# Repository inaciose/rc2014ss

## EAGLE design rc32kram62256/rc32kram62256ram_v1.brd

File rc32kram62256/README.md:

# CNC 3018 - RC2014 - 32K RAM BOARD

This board is done following the schematics of the official RC2014-32K RAM (now retired)

ICs
- 62256 RAM
- 74LS32
- 74LS04

Sockets
- 1 x 28 pin wide DIL
- 1 x 14 pin narrow DIL

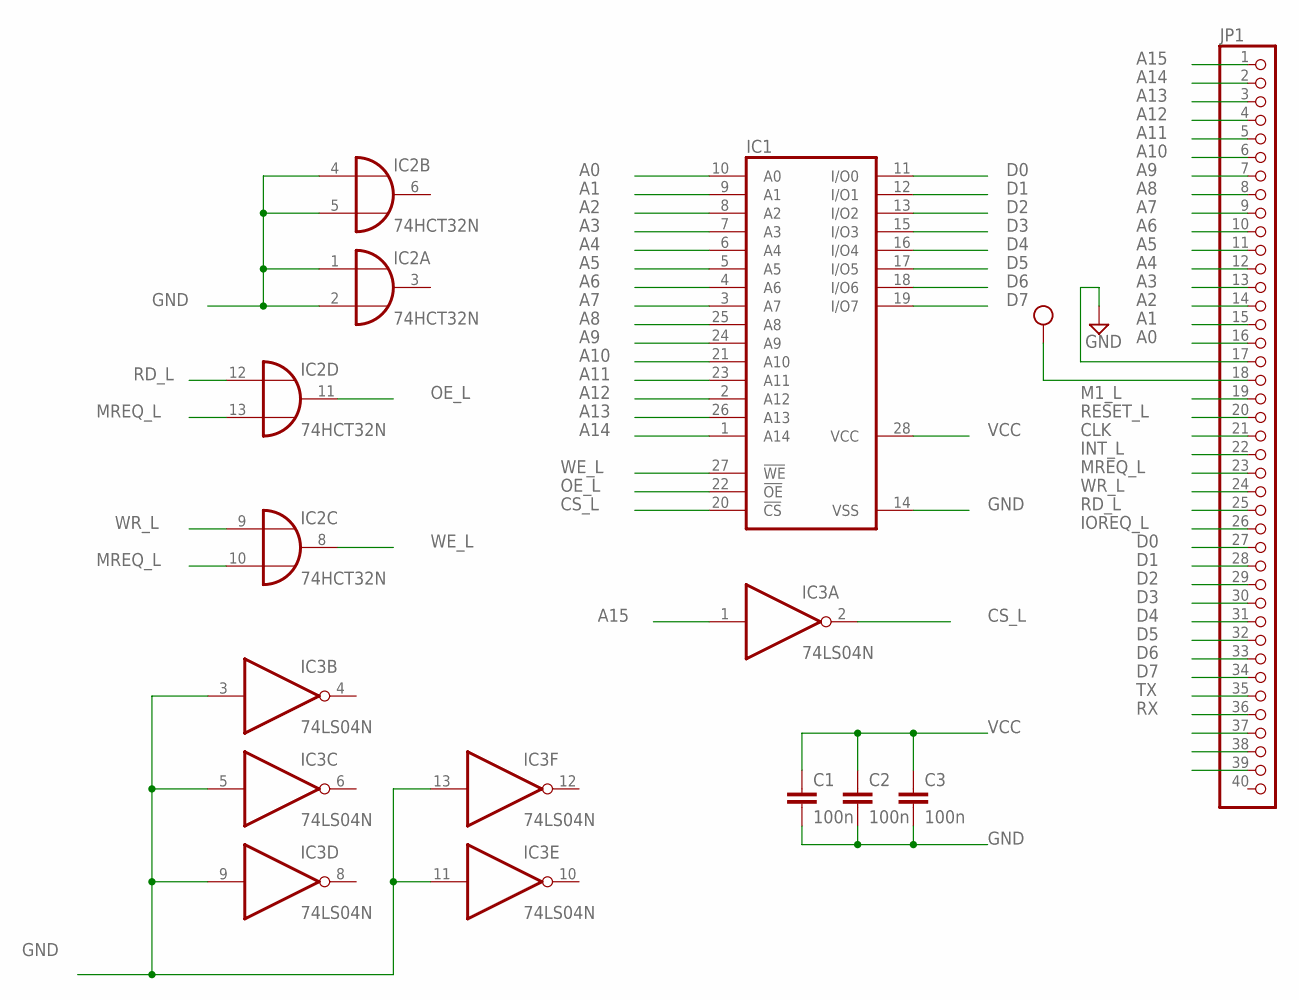
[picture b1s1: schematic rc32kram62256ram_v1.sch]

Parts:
C1, C2, C3: 100n; C050-025X075
IC1: 62256P; DIL28-6
IC2: 74HCT32N; DIL14
IC3: 74LS04N; DIL14
JP1: PINHD-1X40; 1X40

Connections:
A0: IC1.10 (A0), JP1.16
A1: IC1.9 (A1), JP1.15
A2: IC1.8 (A2), JP1.14
A3: IC1.7 (A3), JP1.13
A4: IC1.6 (A4), JP1.12
A5: IC1.5 (A5), JP1.11
A6: IC1.4 (A6), JP1.10
A7: IC1.3 (A7), JP1.9
A8: IC1.25 (A8), JP1.8
A9: IC1.24 (A9), JP1.7
A10: IC1.21 (A10), JP1.6
A11: IC1.23 (A11), JP1.5
A12: IC1.2 (A12), JP1.4
A13: IC1.26 (A13), JP1.3
A14: IC1.1 (A14), JP1.2
A15: IC3.1 (I), JP1.1
CLK: JP1.21
CS_L: IC1.20 (!CS), IC3.2 (O)
D0: IC1.11 (I/O0), JP1.27
D1: IC1.12 (I/O1), JP1.28
D2: IC1.13 (I/O2), JP1.29
D3: IC1.15 (I/O3), JP1.30
D4: IC1.16 (I/O4), JP1.31
D5: IC1.17 (I/O5), JP1.32
D6: IC1.18 (I/O6), JP1.33
D7: IC1.19 (I/O7), JP1.34
GND: C1.2, C2.2, C3.2, IC1.14 (VSS), IC2.1 (I0), IC2.2 (I1), IC2.4 (I0), IC2.5 (I1), IC2.7 (GND), IC3.3 (I), IC3.5 (I), IC3.7 (GND), IC3.9 (I), IC3.11 (I), IC3.13 (I), JP1.17
INT_L: JP1.22
IOREQ_L: JP1.26
M1_L: JP1.19
MREQ_L: IC2.10 (I1), IC2.13 (I1), JP1.23
OE_L: IC1.22 (!OE), IC2.11 (O)
RD_L: IC2.12 (I0), JP1.25
RESET_L: JP1.20
RX: JP1.36
TX: JP1.35
VCC: C1.1, C2.1, C3.1, IC1.28 (VCC), IC2.14 (VCC), IC3.14 (VCC), JP1.18
WE_L: IC1.27 (!WE), IC2.8 (O)
WR_L: IC2.9 (I0), JP1.24

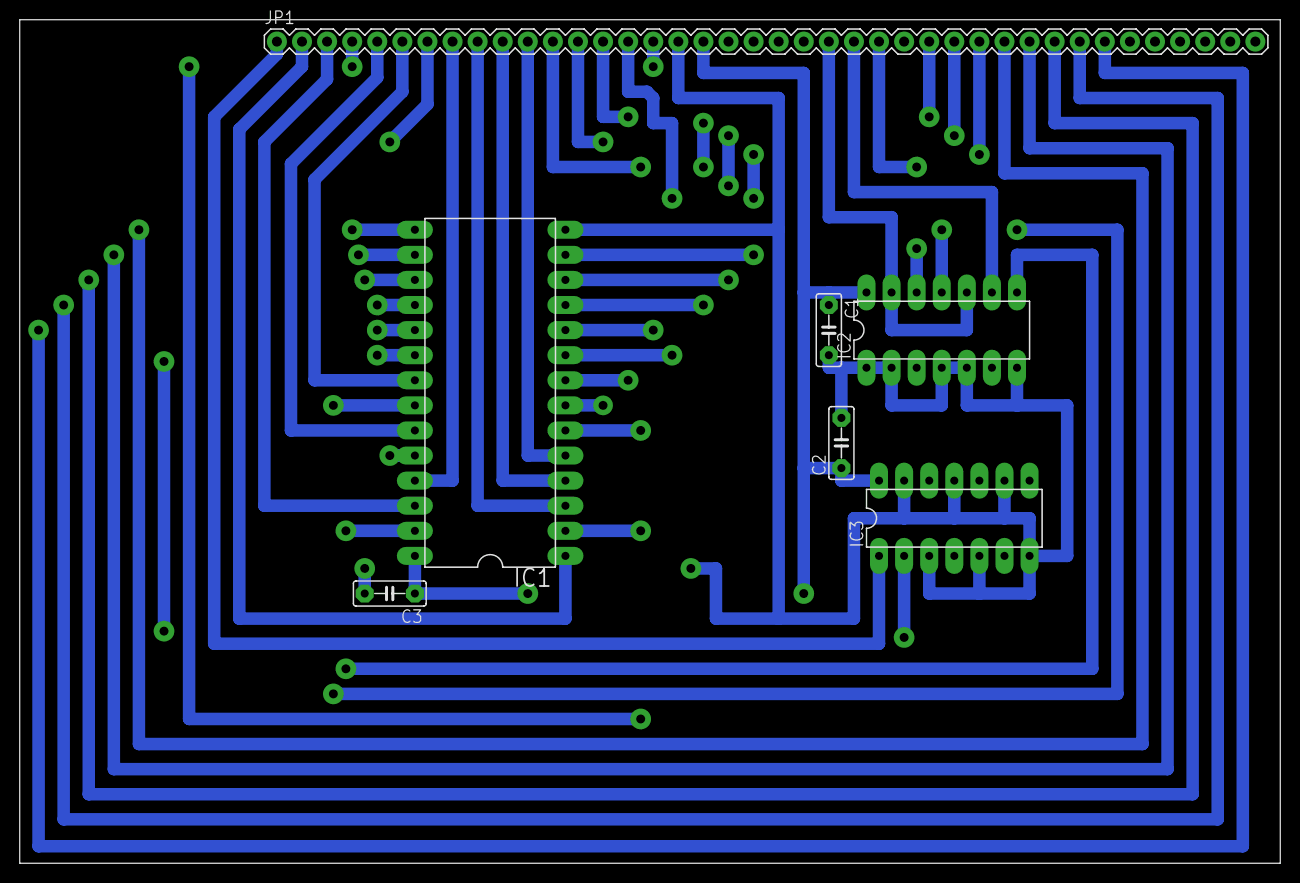
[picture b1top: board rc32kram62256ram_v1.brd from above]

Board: 2 copper layers, 127.6 x 85.4 mm, 7 parts (0 on the bottom side), 32 nets.

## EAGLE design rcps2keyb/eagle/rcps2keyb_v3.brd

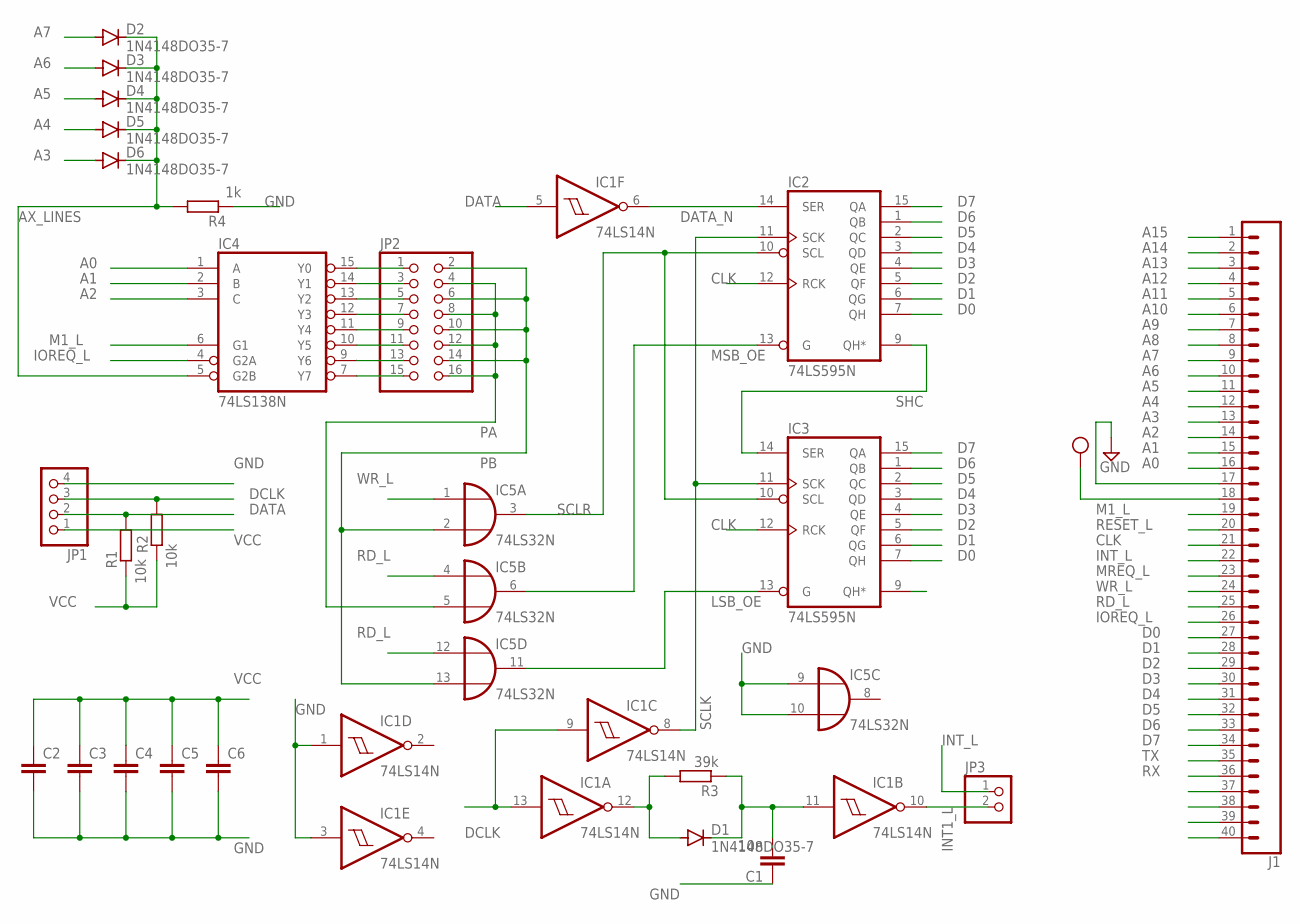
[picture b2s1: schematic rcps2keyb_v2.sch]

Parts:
C1: 10n; C050-025X075
C2, C3, C4, C5, C6: C-EU050-025X075; C050-025X075
D1, D2, D3, D4, D5, D6: 1N4148DO35-7; DO35-7
IC1: 74LS14N; DIL14
IC2, IC3: 74LS595N; DIL16
IC4: 74LS138N; DIL16
IC5: 74LS32N; DIL14
J1: CONN_40OFFSET; 1X40_OFFSET
JP1: PINHD-1X4; 1X04
JP2: PINHD-2X8; 2X08
JP3: PINHD-1X2; 1X02
R1, R2: 10k; 0204/7
R3: 39k; 0204/7
R4: 1k; 0204/7

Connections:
A0: IC4.1 (A), J1.16
A1: IC4.2 (B), J1.15
A2: IC4.3 (C), J1.14
A4: D5.A, J1.12
A5: D4.A, J1.11
A6: D3.A, J1.10
A7: D2.A, J1.9
A8: J1.8
A9: J1.7
A10: J1.6
A11: J1.5
A12: J1.4
A13: J1.3
A14: J1.2
A15: J1.1
CLK: IC2.12 (RCK), IC3.12 (RCK), J1.21
D0: IC2.7 (QH), IC3.7 (QH), J1.27
D1: IC2.6 (QG), IC3.6 (QG), J1.28
D2: IC2.5 (QF), IC3.5 (QF), J1.29
D3: IC2.4 (QE), IC3.4 (QE), J1.30
D4: IC2.3 (QD), IC3.3 (QD), J1.31
D5: IC2.2 (QC), IC3.2 (QC), J1.32
D6: IC2.1 (QB), IC3.1 (QB), J1.33
D7: IC2.15 (QA), IC3.15 (QA), J1.34
DATA: IC1.5 (I), JP1.2, R1.2
DATA_N: IC1.6 (O), IC2.14 (SER)
DCLK: IC1.9 (I), IC1.13 (I), JP1.3, R2.2
GND: C1.1, C2.2, C3.2, C4.2, C5.2, C6.2, IC1.1 (I), IC1.3 (I), IC1.7 (GND), IC2.8 (GND), IC3.8 (GND), IC4.8 (GND), IC5.7 (GND), IC5.9 (I0), IC5.10 (I1), J1.17, JP1.4, R4.1
INT1_L: IC1.10 (O), JP3.2
INT_L: J1.22, JP3.1
IOREQ_L: IC4.4 (G2A), J1.26
LSB_OE: IC3.13 (G), IC5.11 (O)
M1_L: IC4.6 (G1), J1.19
MREQ_L: J1.23
MSB_OE: IC2.13 (G), IC5.6 (O)
unnamed: D1.A, IC1.12 (O), R3.2
unnamed: C1.2, D1.C, IC1.11 (I), R3.1
unnamed: IC4.7 (Y7), JP2.15
unnamed: IC4.9 (Y6), JP2.13
unnamed: IC4.10 (Y5), JP2.11
unnamed: IC4.15 (Y0), JP2.1
unnamed: IC4.14 (Y1), JP2.3
unnamed: IC4.13 (Y2), JP2.5
unnamed: IC4.12 (Y3), JP2.7
unnamed: IC4.11 (Y4), JP2.9
PA: IC5.5 (I1), JP2.4, JP2.8, JP2.12, JP2.16
PB: IC5.2 (I1), IC5.13 (I1), JP2.2, JP2.6, JP2.10, JP2.14
RD_L: IC5.4 (I0), IC5.12 (I0), J1.25
RESET_L: J1.20
RX: J1.36
SCLK: IC1.8 (O), IC2.11 (SCK), IC3.11 (SCK)
SCLR: IC2.10 (SCL), IC3.10 (SCL), IC5.3 (O)
SHC: IC2.9 (QH*), IC3.14 (SER)
TX: J1.35
VCC: C2.1, C3.1, C4.1, C5.1, C6.1, IC1.14 (VCC), IC2.16 (VCC), IC3.16 (VCC), IC4.16 (VCC), IC5.14 (VCC), J1.18, JP1.1, R1.1, R2.1
WR_L: IC5.1 (I0), J1.24

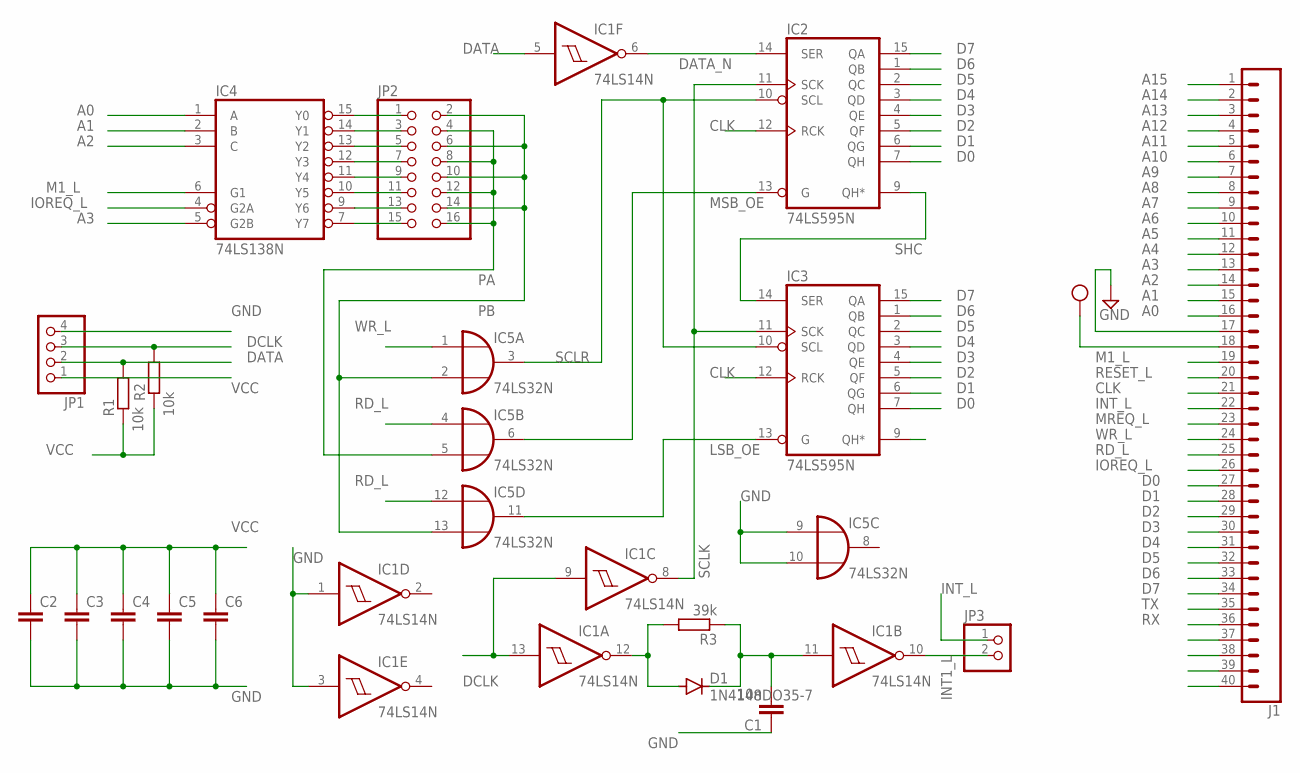
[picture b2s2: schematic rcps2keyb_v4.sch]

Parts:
C1: 10n; C050-025X075
C2, C3, C4, C5, C6: C-EU050-025X075; C050-025X075
D1: 1N4148DO35-7; DO35-7
IC1: 74LS14N; DIL14
IC2, IC3: 74LS595N; DIL16
IC4: 74LS138N; DIL16
IC5: 74LS32N; DIL14
J1: CONN_40OFFSET; 1X40_OFFSET
JP1: PINHD-1X4; 1X04
JP2: PINHD-2X8; 2X08
JP3: PINHD-1X2; 1X02
R1, R2: 10k; 0204/7
R3: 39k; 0204/7

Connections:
A0: IC4.1 (A), J1.16
A1: IC4.2 (B), J1.15
A2: IC4.3 (C), J1.14
A4: J1.12; also elsewhere on the board
A5: J1.11; also elsewhere on the board
A6: J1.10; also elsewhere on the board
A7: J1.9; also elsewhere on the board
A8: J1.8
A9: J1.7
A10: J1.6
A11: J1.5
A12: J1.4
A13: J1.3
A14: J1.2
A15: J1.1
CLK: IC2.12 (RCK), IC3.12 (RCK), J1.21
D0: IC2.7 (QH), IC3.7 (QH), J1.27
D1: IC2.6 (QG), IC3.6 (QG), J1.28
D2: IC2.5 (QF), IC3.5 (QF), J1.29
D3: IC2.4 (QE), IC3.4 (QE), J1.30
D4: IC2.3 (QD), IC3.3 (QD), J1.31
D5: IC2.2 (QC), IC3.2 (QC), J1.32
D6: IC2.1 (QB), IC3.1 (QB), J1.33
D7: IC2.15 (QA), IC3.15 (QA), J1.34
DATA: IC1.5 (I), JP1.2, R1.2
DATA_N: IC1.6 (O), IC2.14 (SER)
DCLK: IC1.9 (I), IC1.13 (I), JP1.3, R2.2
GND: C1.1, C2.2, C3.2, C4.2, C5.2, C6.2, IC1.1 (I), IC1.3 (I), IC1.7 (GND), IC2.8 (GND), IC3.8 (GND), IC4.8 (GND), IC5.7 (GND), IC5.9 (I0), IC5.10 (I1), J1.17, JP1.4; also elsewhere on the board
INT1_L: IC1.10 (O), JP3.2
INT_L: J1.22, JP3.1
IOREQ_L: IC4.4 (G2A), J1.26
LSB_OE: IC3.13 (G), IC5.11 (O)
M1_L: IC4.6 (G1), J1.19
MREQ_L: J1.23
MSB_OE: IC2.13 (G), IC5.6 (O)
unnamed: D1.A, IC1.12 (O), R3.2
unnamed: C1.2, D1.C, IC1.11 (I), R3.1
unnamed: IC4.7 (Y7), JP2.15
unnamed: IC4.9 (Y6), JP2.13
unnamed: IC4.10 (Y5), JP2.11
unnamed: IC4.15 (Y0), JP2.1
unnamed: IC4.14 (Y1), JP2.3
unnamed: IC4.13 (Y2), JP2.5
unnamed: IC4.12 (Y3), JP2.7
unnamed: IC4.11 (Y4), JP2.9
PA: IC5.5 (I1), JP2.4, JP2.8, JP2.12, JP2.16
PB: IC5.2 (I1), IC5.13 (I1), JP2.2, JP2.6, JP2.10, JP2.14
RD_L: IC5.4 (I0), IC5.12 (I0), J1.25
RESET_L: J1.20
RX: J1.36
SCLK: IC1.8 (O), IC2.11 (SCK), IC3.11 (SCK)
SCLR: IC2.10 (SCL), IC3.10 (SCL), IC5.3 (O)
SHC: IC2.9 (QH*), IC3.14 (SER)
TX: J1.35
VCC: C2.1, C3.1, C4.1, C5.1, C6.1, IC1.14 (VCC), IC2.16 (VCC), IC3.16 (VCC), IC4.16 (VCC), IC5.14 (VCC), J1.18, JP1.1, R1.1, R2.1
WR_L: IC5.1 (I0), J1.24

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
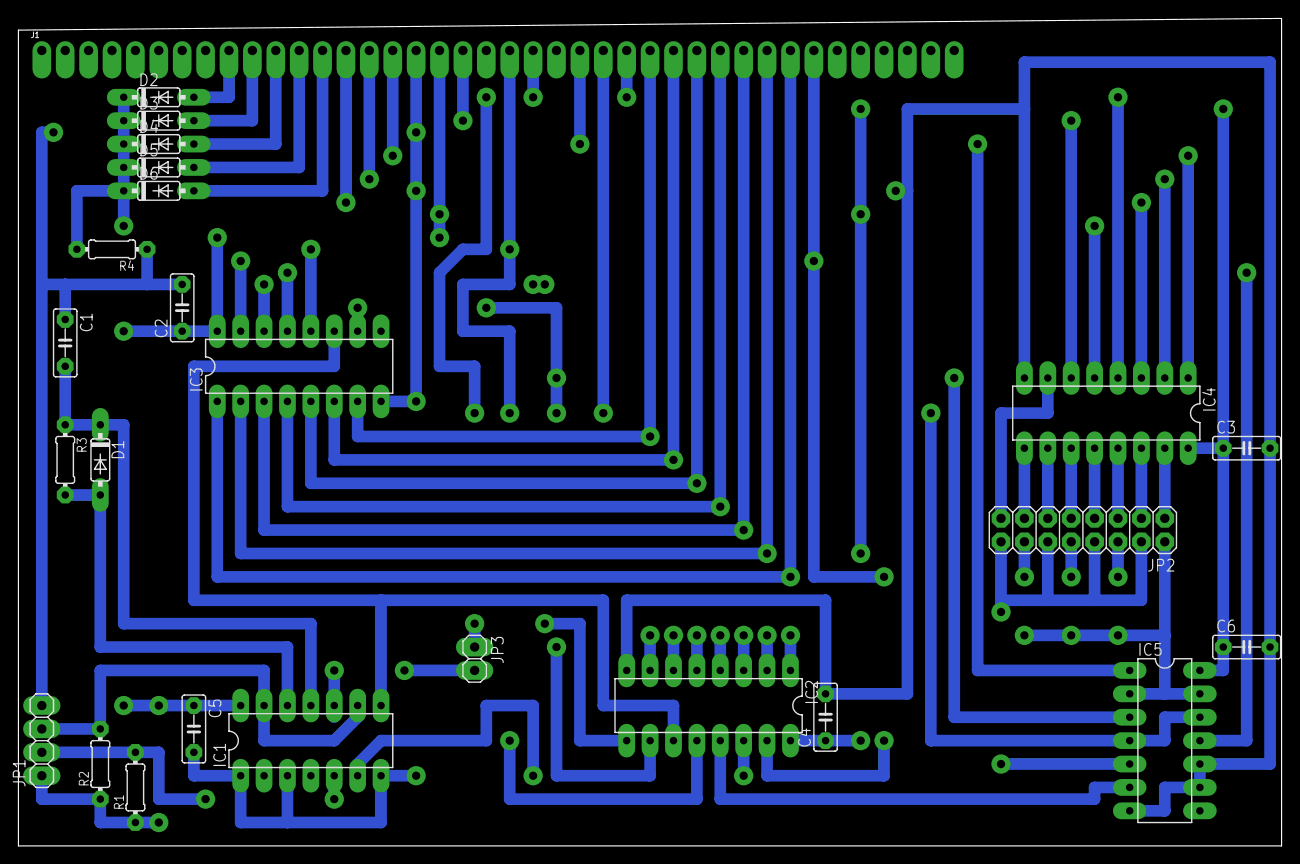
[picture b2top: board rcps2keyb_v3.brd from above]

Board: 2 copper layers, 137.1 x 89.8 mm, 25 parts (0 on the bottom side), 46 nets.

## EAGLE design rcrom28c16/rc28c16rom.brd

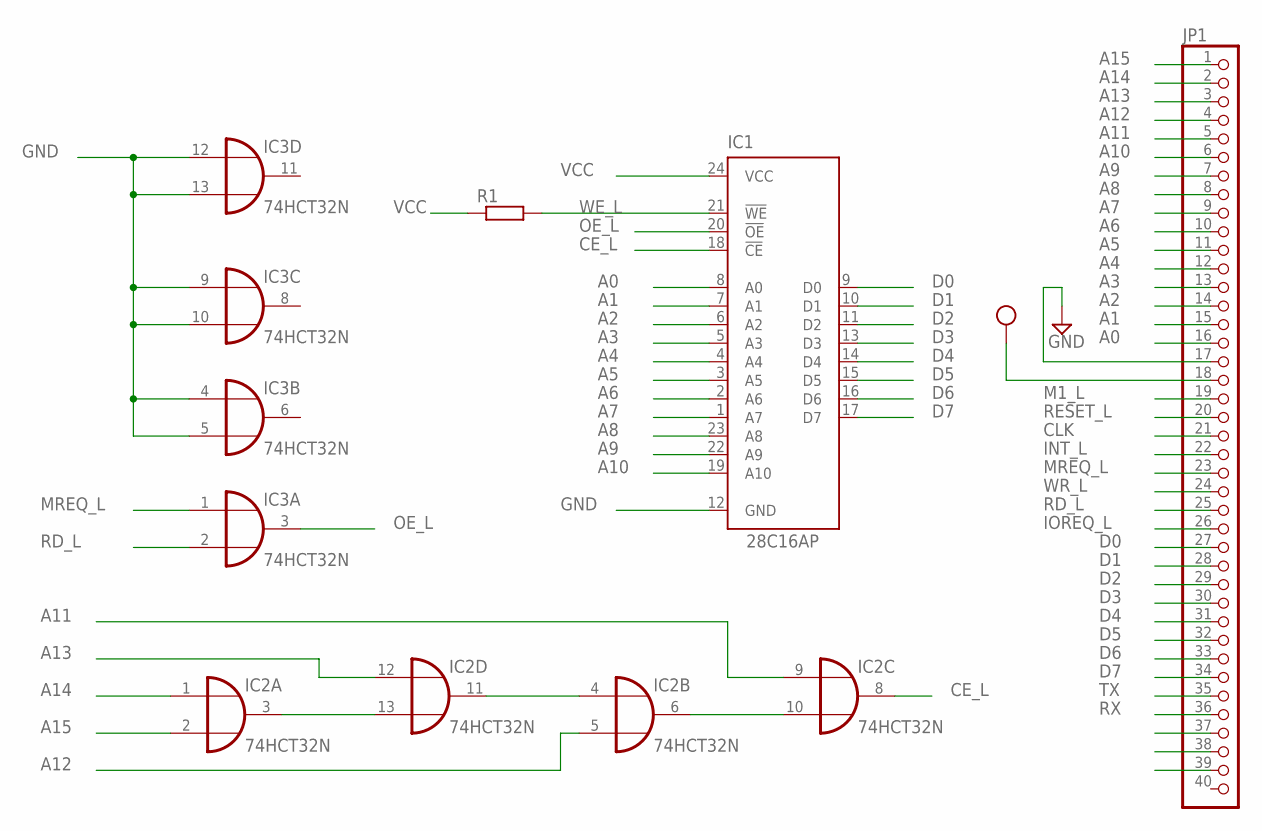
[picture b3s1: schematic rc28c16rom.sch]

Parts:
IC1: 28C16AP; DIL24-6
IC2, IC3: 74HCT32N; DIL14
JP1: PINHD-1X40; 1X40
R1: R-EU_0204/5; 0204/5

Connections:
A0: IC1.8 (A0), JP1.16
A1: IC1.7 (A1), JP1.15
A2: IC1.6 (A2), JP1.14
A3: IC1.5 (A3), JP1.13
A4: IC1.4 (A4), JP1.12
A5: IC1.3 (A5), JP1.11
A6: IC1.2 (A6), JP1.10
A7: IC1.1 (A7), JP1.9
A8: IC1.23 (A8), JP1.8
A9: IC1.22 (A9), JP1.7
A10: IC1.19 (A10), JP1.6
A11: IC2.9 (I0), JP1.5
A12: IC2.5 (I1), JP1.4
A13: IC2.12 (I0), JP1.3
A14: IC2.1 (I0), JP1.2
A15: IC2.2 (I1), JP1.1
CE_L: IC1.18 (!CE), IC2.8 (O)
CLK: JP1.21
D0: IC1.9 (D0), JP1.27
D1: IC1.10 (D1), JP1.28
D2: IC1.11 (D2), JP1.29
D3: IC1.13 (D3), JP1.30
D4: IC1.14 (D4), JP1.31
D5: IC1.15 (D5), JP1.32
D6: IC1.16 (D6), JP1.33
D7: IC1.17 (D7), JP1.34
GND: IC1.12 (GND), IC2.7 (GND), IC3.4 (I0), IC3.5 (I1), IC3.7 (GND), IC3.9 (I0), IC3.10 (I1), IC3.12 (I0), IC3.13 (I1), JP1.17
INT_L: JP1.22
IOREQ_L: JP1.26
M1_L: JP1.19
MREQ_L: IC3.1 (I0), JP1.23
unnamed: IC2.6 (O), IC2.10 (I1)
unnamed: IC2.3 (O), IC2.13 (I1)
unnamed: IC2.4 (I0), IC2.11 (O)
OE_L: IC1.20 (!OE), IC3.3 (O)
RD_L: IC3.2 (I1), JP1.25
RESET_L: JP1.20
RX: JP1.36
TX: JP1.35
VCC: IC1.24 (VCC), IC2.14 (VCC), IC3.14 (VCC), JP1.18, R1.1
WE_L: IC1.21 (!WE), R1.2
WR_L: JP1.24

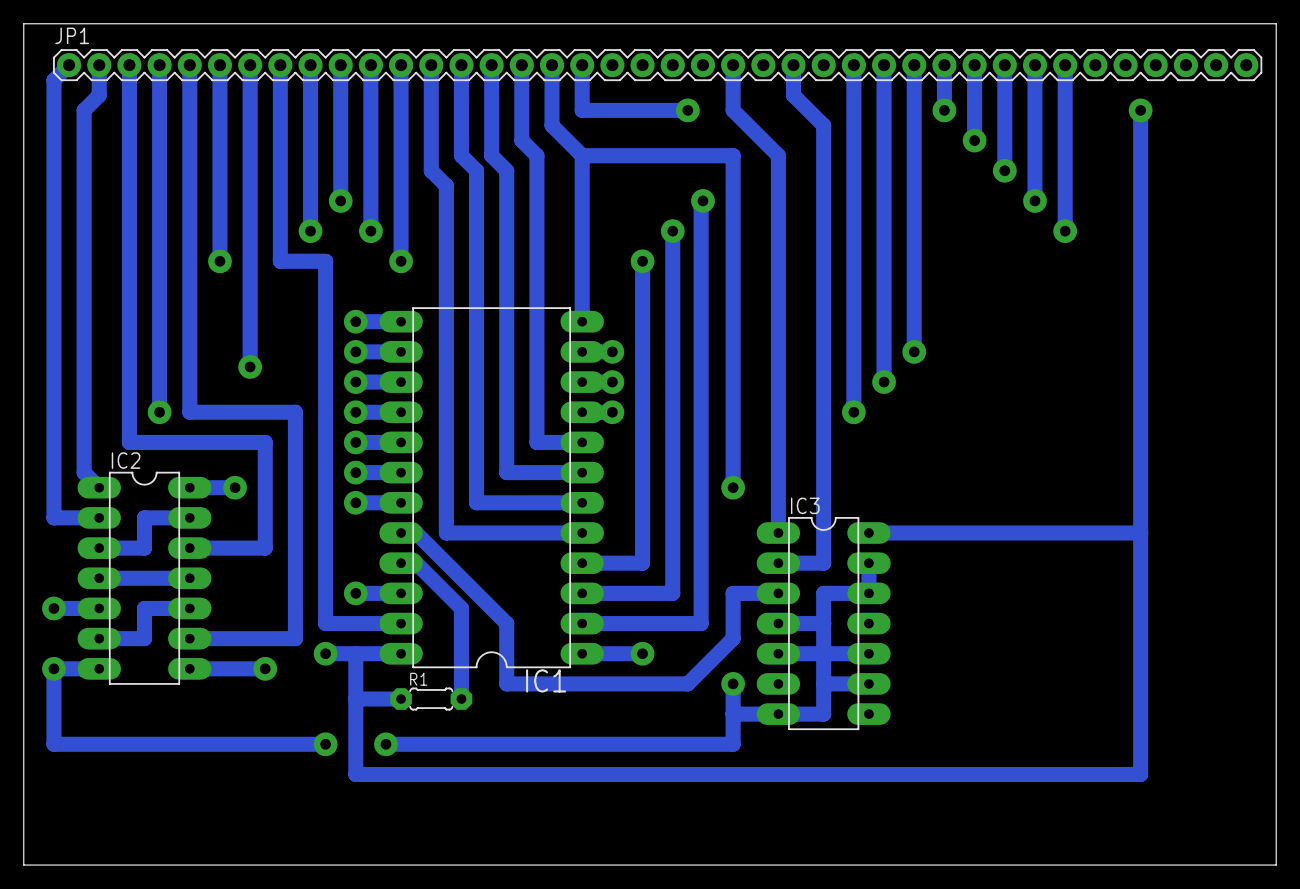
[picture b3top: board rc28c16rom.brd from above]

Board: 2 copper layers, 105.4 x 70.8 mm, 5 parts (0 on the bottom side), 34 nets.

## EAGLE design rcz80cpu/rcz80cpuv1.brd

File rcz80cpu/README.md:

# CNC 3018 - RC2014 - Z80 BOARD

This board is done with some changes to the schematics of the oficial old RC2014 CPU board

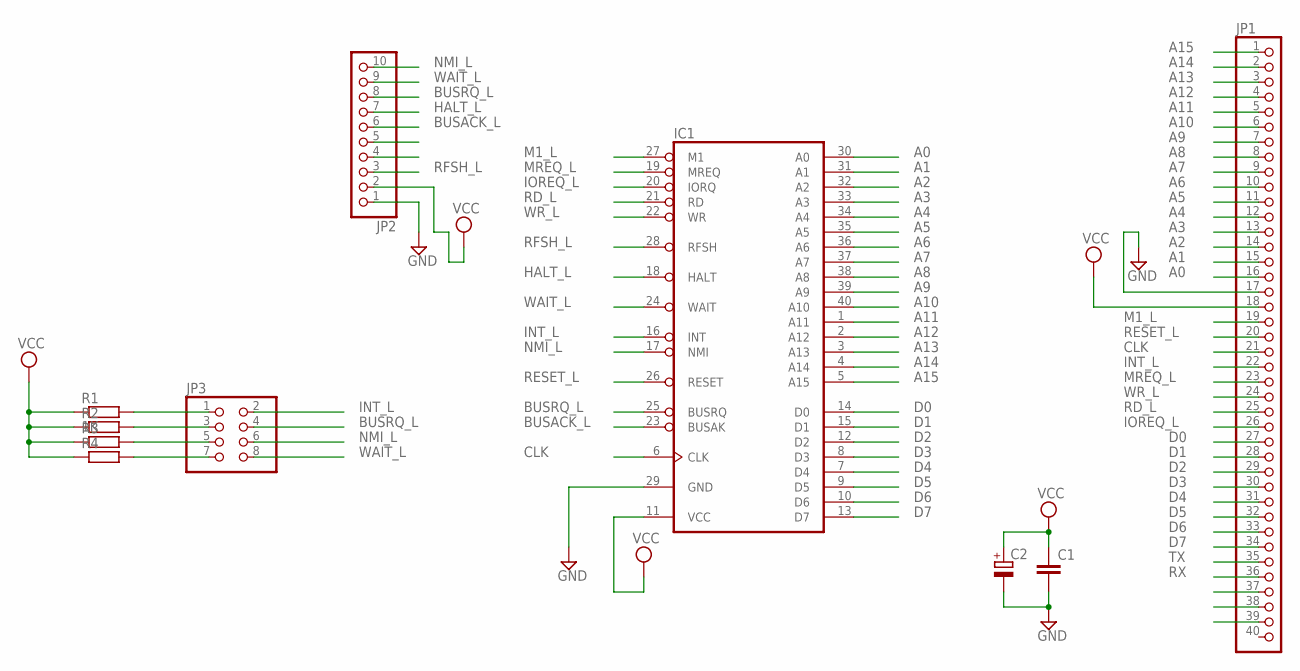
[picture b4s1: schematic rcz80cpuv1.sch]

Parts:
C1: C-EU025-024X044; C025-024X044
C2: CPOL-EUE2,5-6E; E2,5-6E
IC1: Z80CPU; DIL40
JP1: PINHD-1X40; 1X40
JP2: PINHD-1X10; 1X10
JP3: PINHD-2X4; 2X04
R1: 1K; 0204/7
R2, R3, R4: R-EU_0204/7; 0204/7

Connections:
A0: IC1.30 (A0), JP1.16
A1: IC1.31 (A1), JP1.15
A2: IC1.32 (A2), JP1.14
A3: IC1.33 (A3), JP1.13
A4: IC1.34 (A4), JP1.12
A5: IC1.35 (A5), JP1.11
A6: IC1.36 (A6), JP1.10
A7: IC1.37 (A7), JP1.9
A8: IC1.38 (A8), JP1.8
A9: IC1.39 (A9), JP1.7
A10: IC1.40 (A10), JP1.6
A11: IC1.1 (A11), JP1.5
A12: IC1.2 (A12), JP1.4
A13: IC1.3 (A13), JP1.3
A14: IC1.4 (A14), JP1.2
A15: IC1.5 (A15), JP1.1
BUSACK_L: IC1.23 (BUSAK), JP2.6
BUSRQ_L: IC1.25 (BUSRQ), JP2.8, JP3.4
CLK: IC1.6 (CLK), JP1.21
D0: IC1.14 (D0), JP1.27
D1: IC1.15 (D1), JP1.28
D2: IC1.12 (D2), JP1.29
D3: IC1.8 (D3), JP1.30
D4: IC1.7 (D4), JP1.31
D5: IC1.9 (D5), JP1.32
D6: IC1.10 (D6), JP1.33
D7: IC1.13 (D7), JP1.34
GND: C1.2, C2.-, IC1.29 (GND), JP1.17, JP2.1
HALT_L: IC1.18 (HALT), JP2.7
INT_L: IC1.16 (INT), JP1.22, JP3.2
IOREQ_L: IC1.20 (IORQ), JP1.26
M1_L: IC1.27 (M1), JP1.19
MREQ_L: IC1.19 (MREQ), JP1.23
unnamed: JP3.1, R1.2
unnamed: JP3.3, R2.2
unnamed: JP3.5, R3.2
unnamed: JP3.7, R4.2
NMI_L: IC1.17 (NMI), JP2.10, JP3.6
RD_L: IC1.21 (RD), JP1.25
RESET_L: IC1.26 (RESET), JP1.20
RFSH_L: IC1.28 (RFSH), JP2.3
RX: JP1.36
TX: JP1.35
VCC: C1.1, C2.+, IC1.11 (VCC), JP1.18, JP2.2, R1.1, R2.1, R3.1, R4.1
WAIT_L: IC1.24 (WAIT), JP2.9, JP3.8
WR_L: IC1.22 (WR), JP1.24

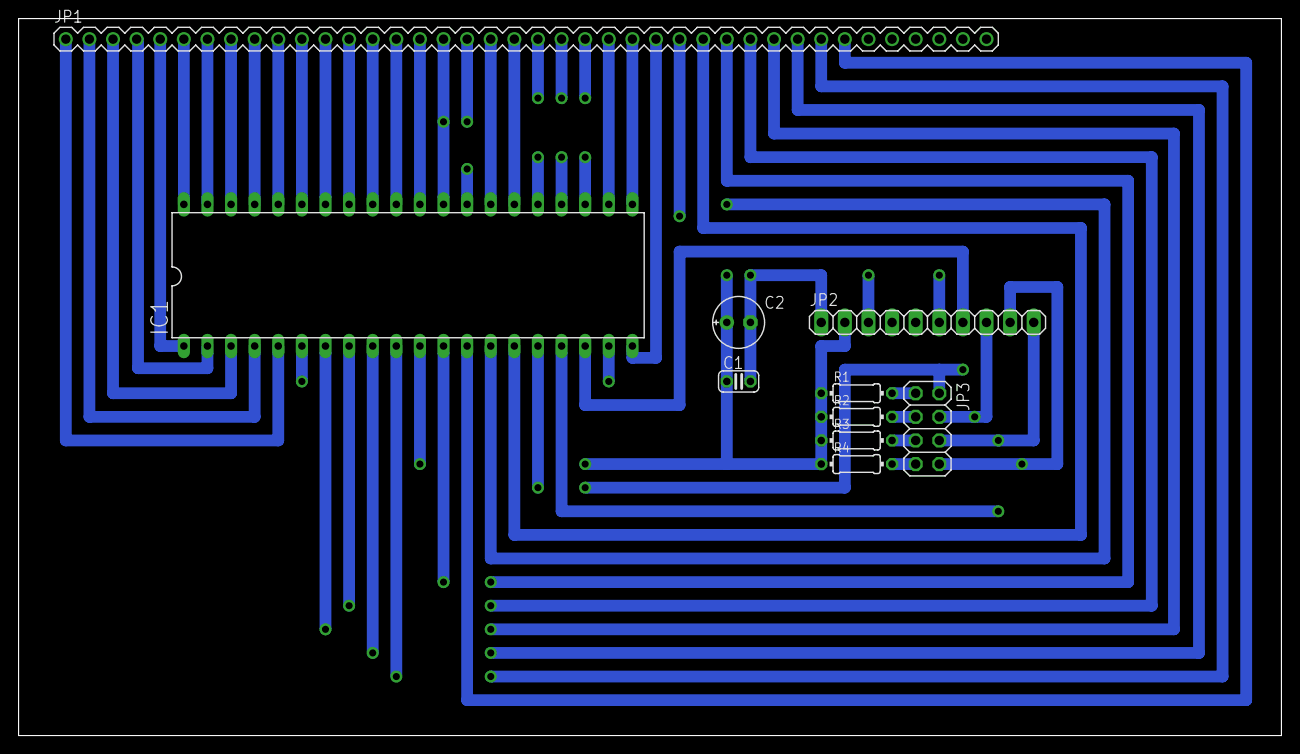
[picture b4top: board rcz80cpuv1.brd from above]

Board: 2 copper layers, 135.9 x 77.1 mm, 10 parts (0 on the bottom side), 44 nets.

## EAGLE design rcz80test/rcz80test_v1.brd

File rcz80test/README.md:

# CNC 3018 - RC2014 - Z80 TESTER

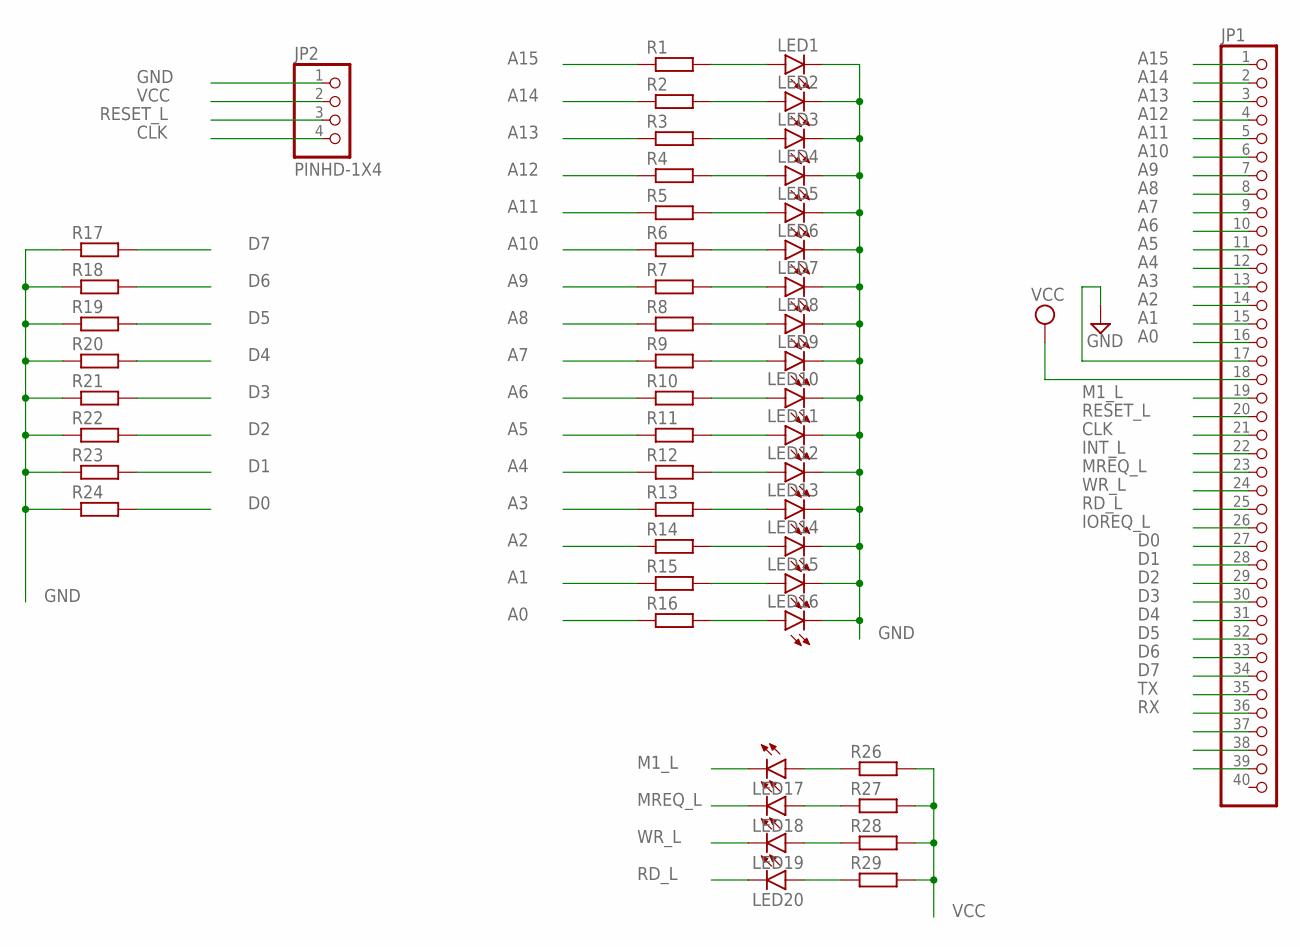
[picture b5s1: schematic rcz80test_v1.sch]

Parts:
JP1: PINHD-1X40; 1X40
JP2: PINHD-1X4; 1X04
LED1, LED2, LED3, LED4, LED5, LED6, LED7, LED8, LED9, LED10, LED11, LED12, LED13, LED14, LED15, LED16, LED17, LED18, LED19, LED20: LED3MM
R1, R2, R3, R4, R5, R6, R7, R8, R9, R10, R11, R12, R13, R14, R15, R16, R17, R18, R19, R20, R21, R22, R23, R24, R26, R27, R28, R29: R-EU_0204/7; 0204/7

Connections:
A0: JP1.16, R16.1
A1: JP1.15, R15.1
A2: JP1.14, R14.1
A3: JP1.13, R13.1
A4: JP1.12, R12.1
A5: JP1.11, R11.1
A6: JP1.10, R10.1
A7: JP1.9, R9.1
A8: JP1.8, R8.1
A9: JP1.7, R7.1
A10: JP1.6, R6.1
A11: JP1.5, R5.1
A12: JP1.4, R4.1
A13: JP1.3, R3.1
A14: JP1.2, R2.1
A15: JP1.1, R1.1
CLK: JP1.21, JP2.4
D0: JP1.27, R24.2
D1: JP1.28, R23.2
D2: JP1.29, R22.2
D3: JP1.30, R21.2
D4: JP1.31, R20.2
D5: JP1.32, R19.2
D6: JP1.33, R18.2
D7: JP1.34, R17.2
GND: JP1.17, JP2.1, LED1.K (C), LED2.K (C), LED3.K (C), LED4.K (C), LED5.K (C), LED6.K (C), LED7.K (C), LED8.K (C), LED9.K (C), LED10.K (C), LED11.K (C), LED12.K (C), LED13.K (C), LED14.K (C), LED15.K (C), LED16.K (C), R17.1, R18.1, R19.1, R20.1, R21.1, R22.1, R23.1, R24.1
INT_L: JP1.22
IOREQ_L: JP1.26
M1_L: JP1.19, LED17.K (C)
MREQ_L: JP1.23, LED18.K (C)
unnamed: LED17.A, R26.1
unnamed: LED18.A, R27.1
unnamed: LED19.A, R28.1
unnamed: LED20.A, R29.1
unnamed: LED1.A, R1.2
unnamed: LED16.A, R16.2
unnamed: LED15.A, R15.2
unnamed: LED14.A, R14.2
unnamed: LED13.A, R13.2
unnamed: LED12.A, R12.2
unnamed: LED11.A, R11.2
unnamed: LED10.A, R10.2
unnamed: LED9.A, R9.2
unnamed: LED8.A, R8.2
unnamed: LED7.A, R7.2
unnamed: LED6.A, R6.2
unnamed: LED5.A, R5.2
unnamed: LED4.A, R4.2
unnamed: LED3.A, R3.2
unnamed: LED2.A, R2.2
RD_L: JP1.25, LED20.K (C)
RESET_L: JP1.20, JP2.3
RX: JP1.36
TX: JP1.35
VCC: JP1.18, JP2.2, R26.2, R27.2, R28.2, R29.2
WR_L: JP1.24, LED19.K (C)

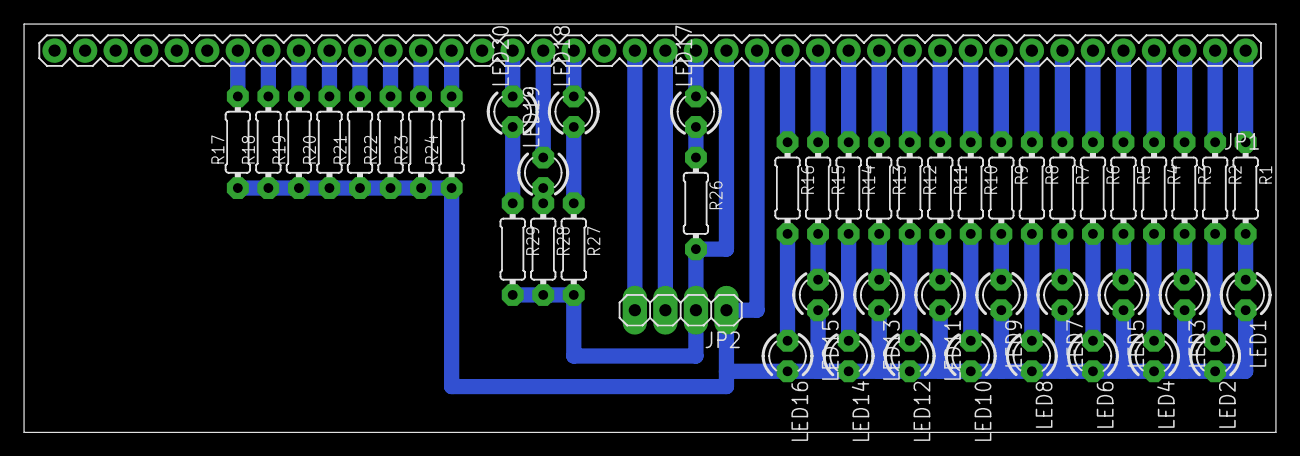
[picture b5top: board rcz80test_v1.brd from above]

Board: 2 copper layers, 104.1 x 34.0 mm, 50 parts (0 on the bottom side), 52 nets.

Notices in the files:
parts and their libraries:
SparkFun-Connectors: Licensing: Creative Commons ShareAlike 4.0 International - https://creativecommons.org/licenses/by-sa/4.0
